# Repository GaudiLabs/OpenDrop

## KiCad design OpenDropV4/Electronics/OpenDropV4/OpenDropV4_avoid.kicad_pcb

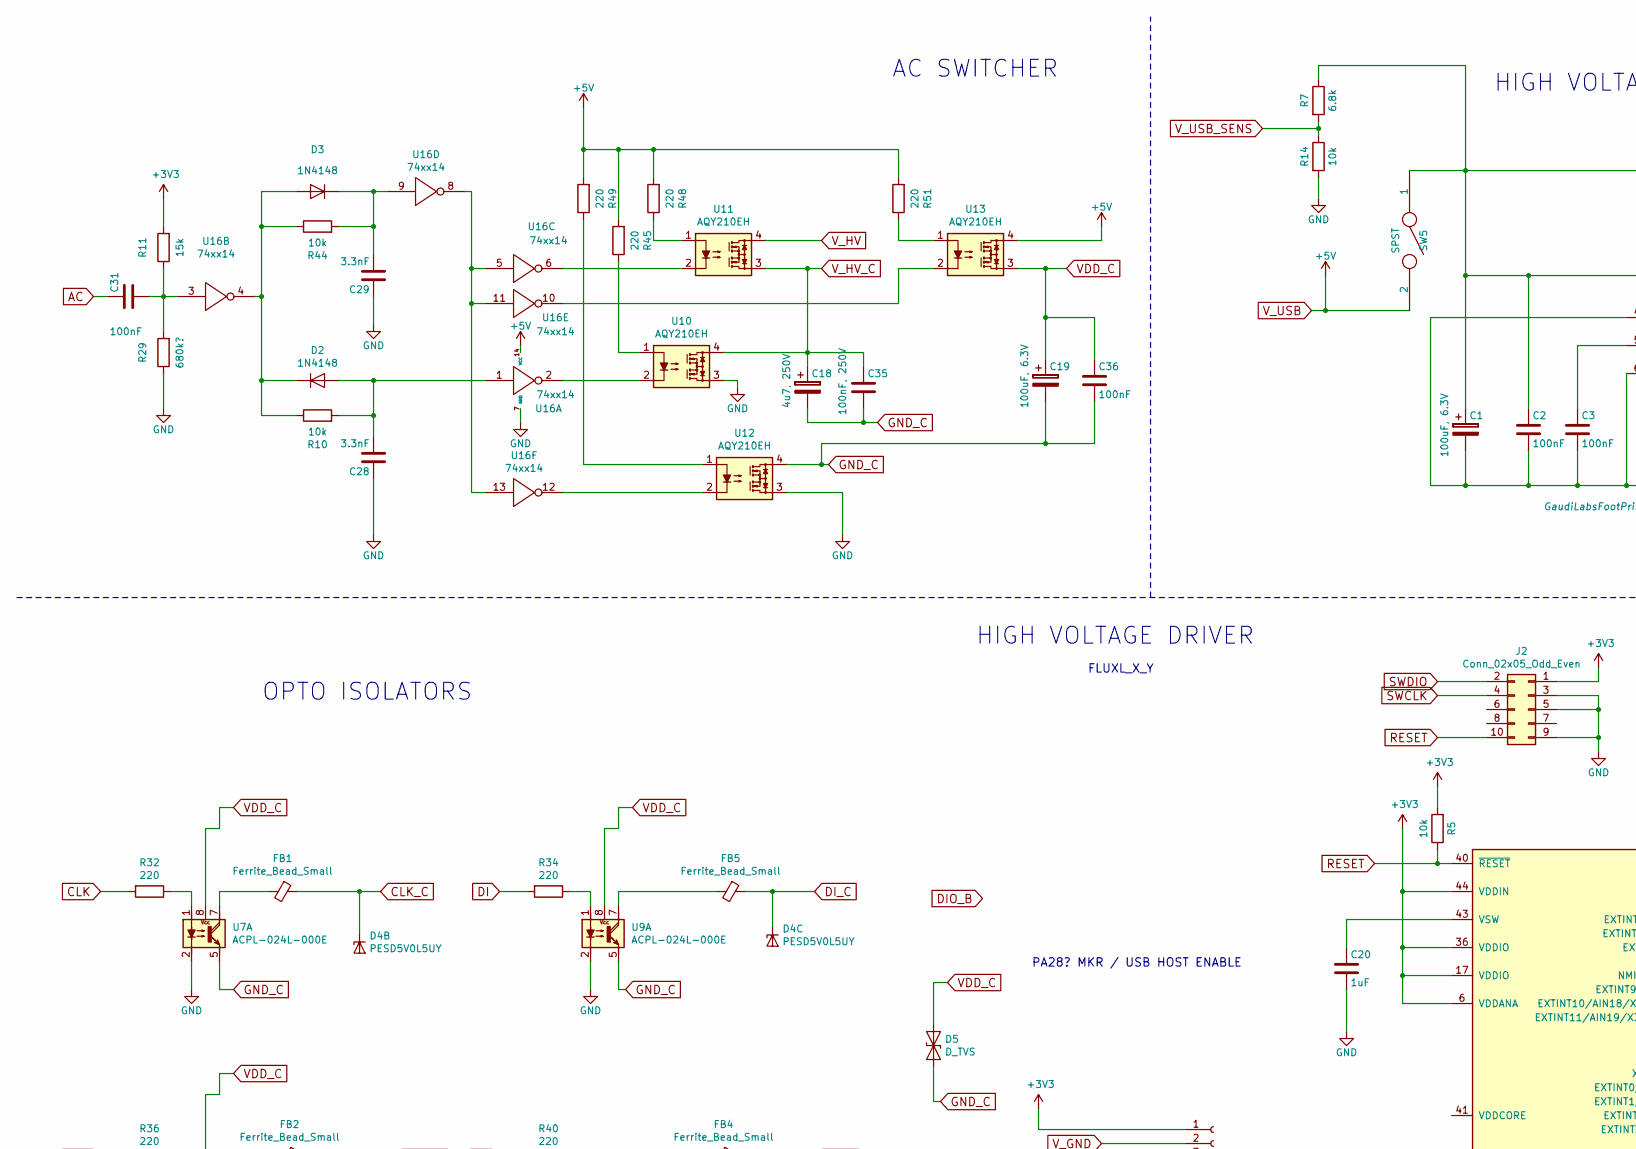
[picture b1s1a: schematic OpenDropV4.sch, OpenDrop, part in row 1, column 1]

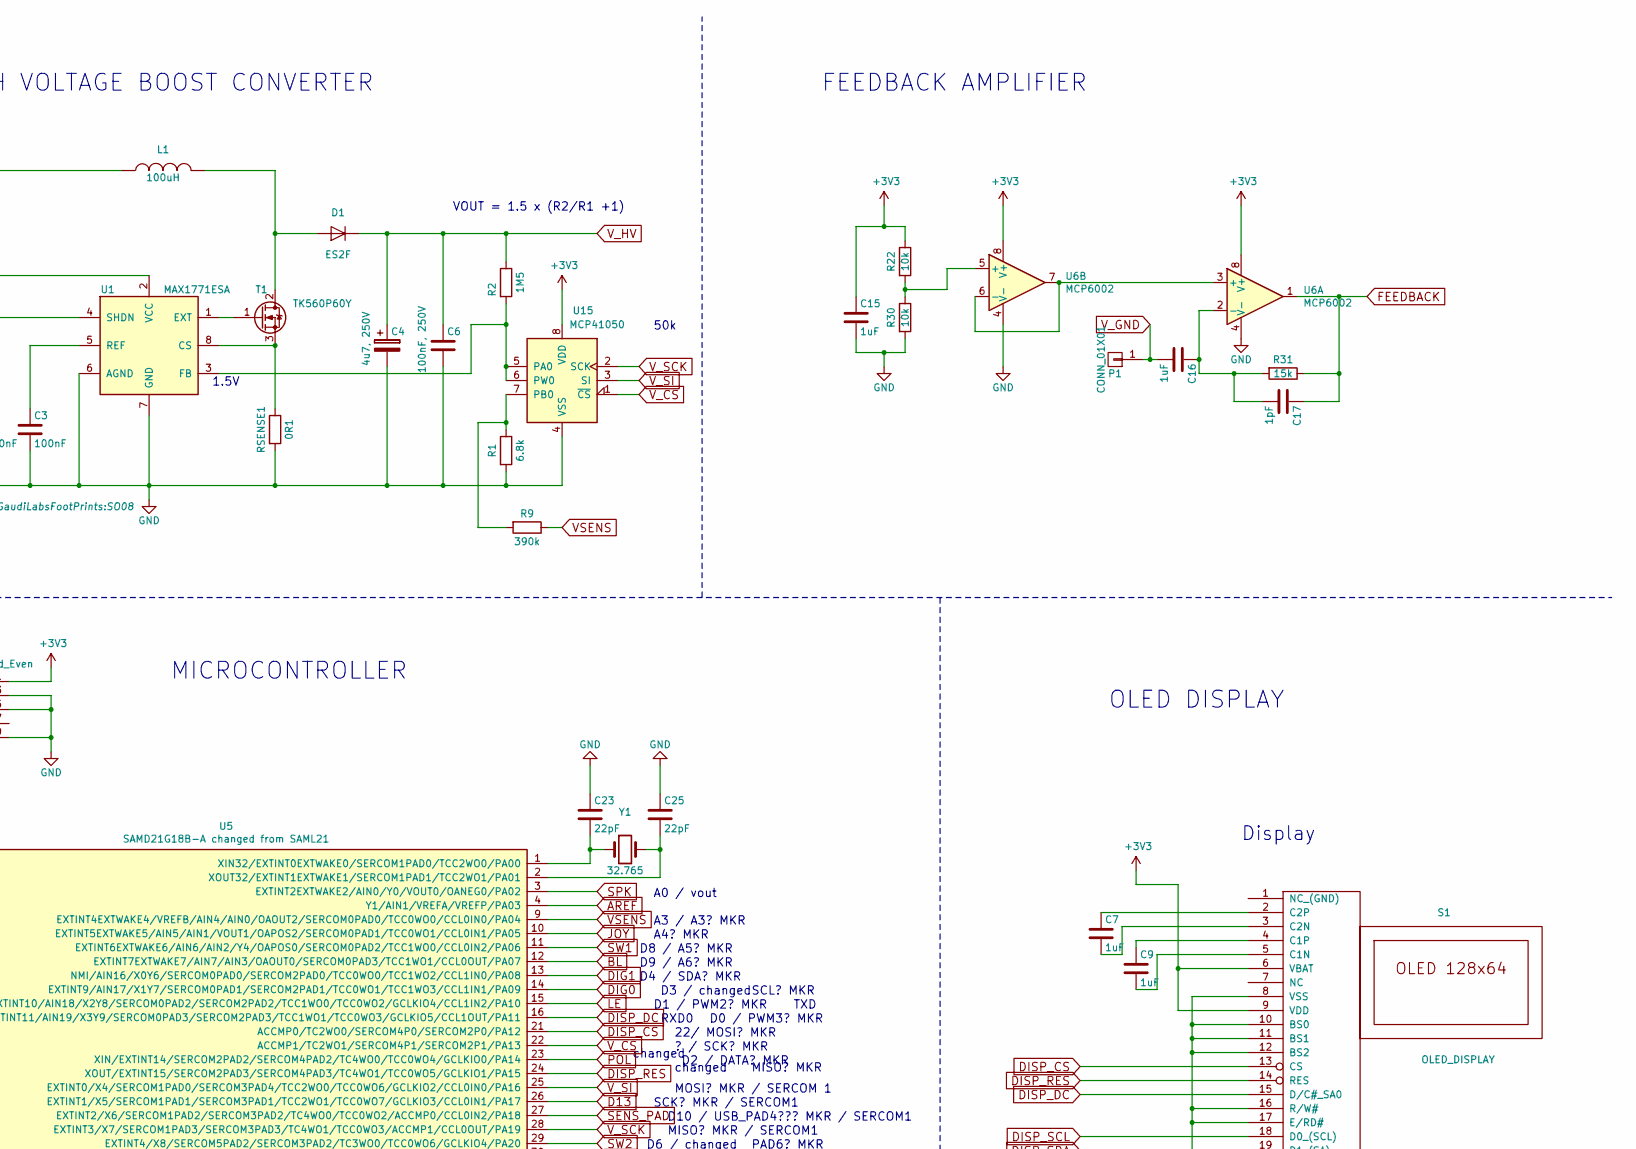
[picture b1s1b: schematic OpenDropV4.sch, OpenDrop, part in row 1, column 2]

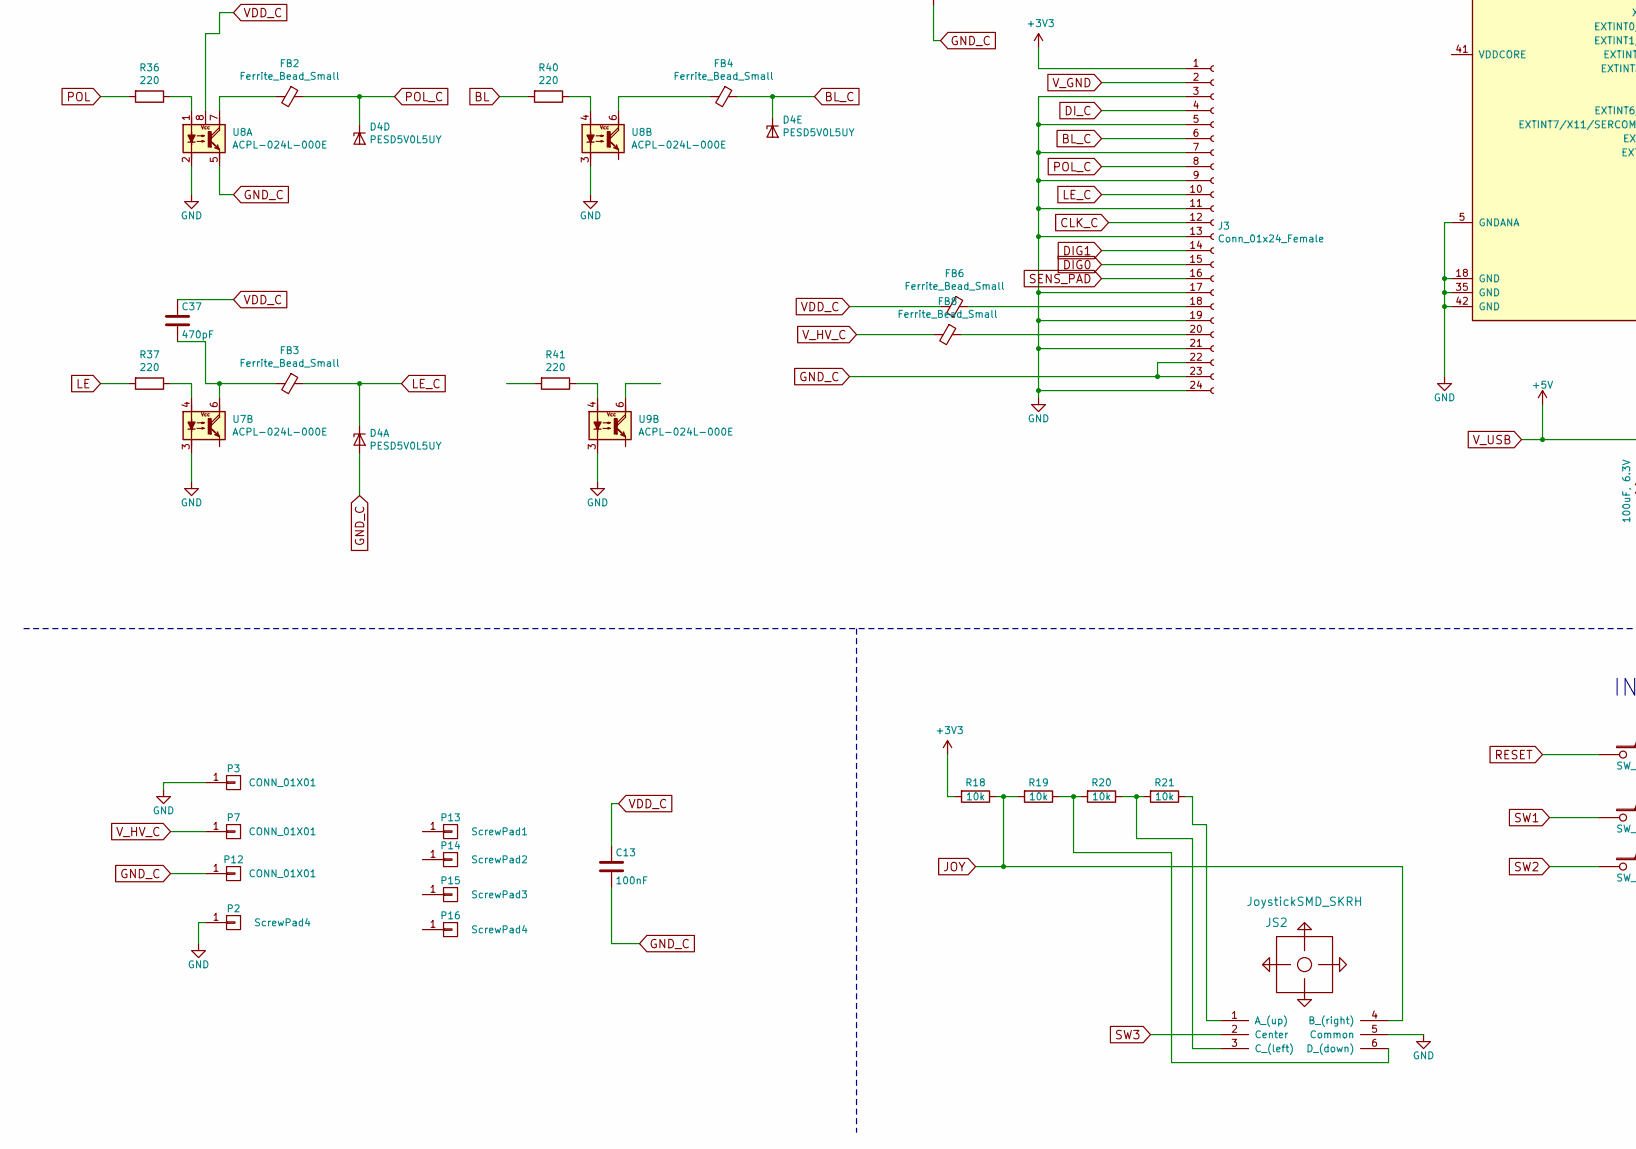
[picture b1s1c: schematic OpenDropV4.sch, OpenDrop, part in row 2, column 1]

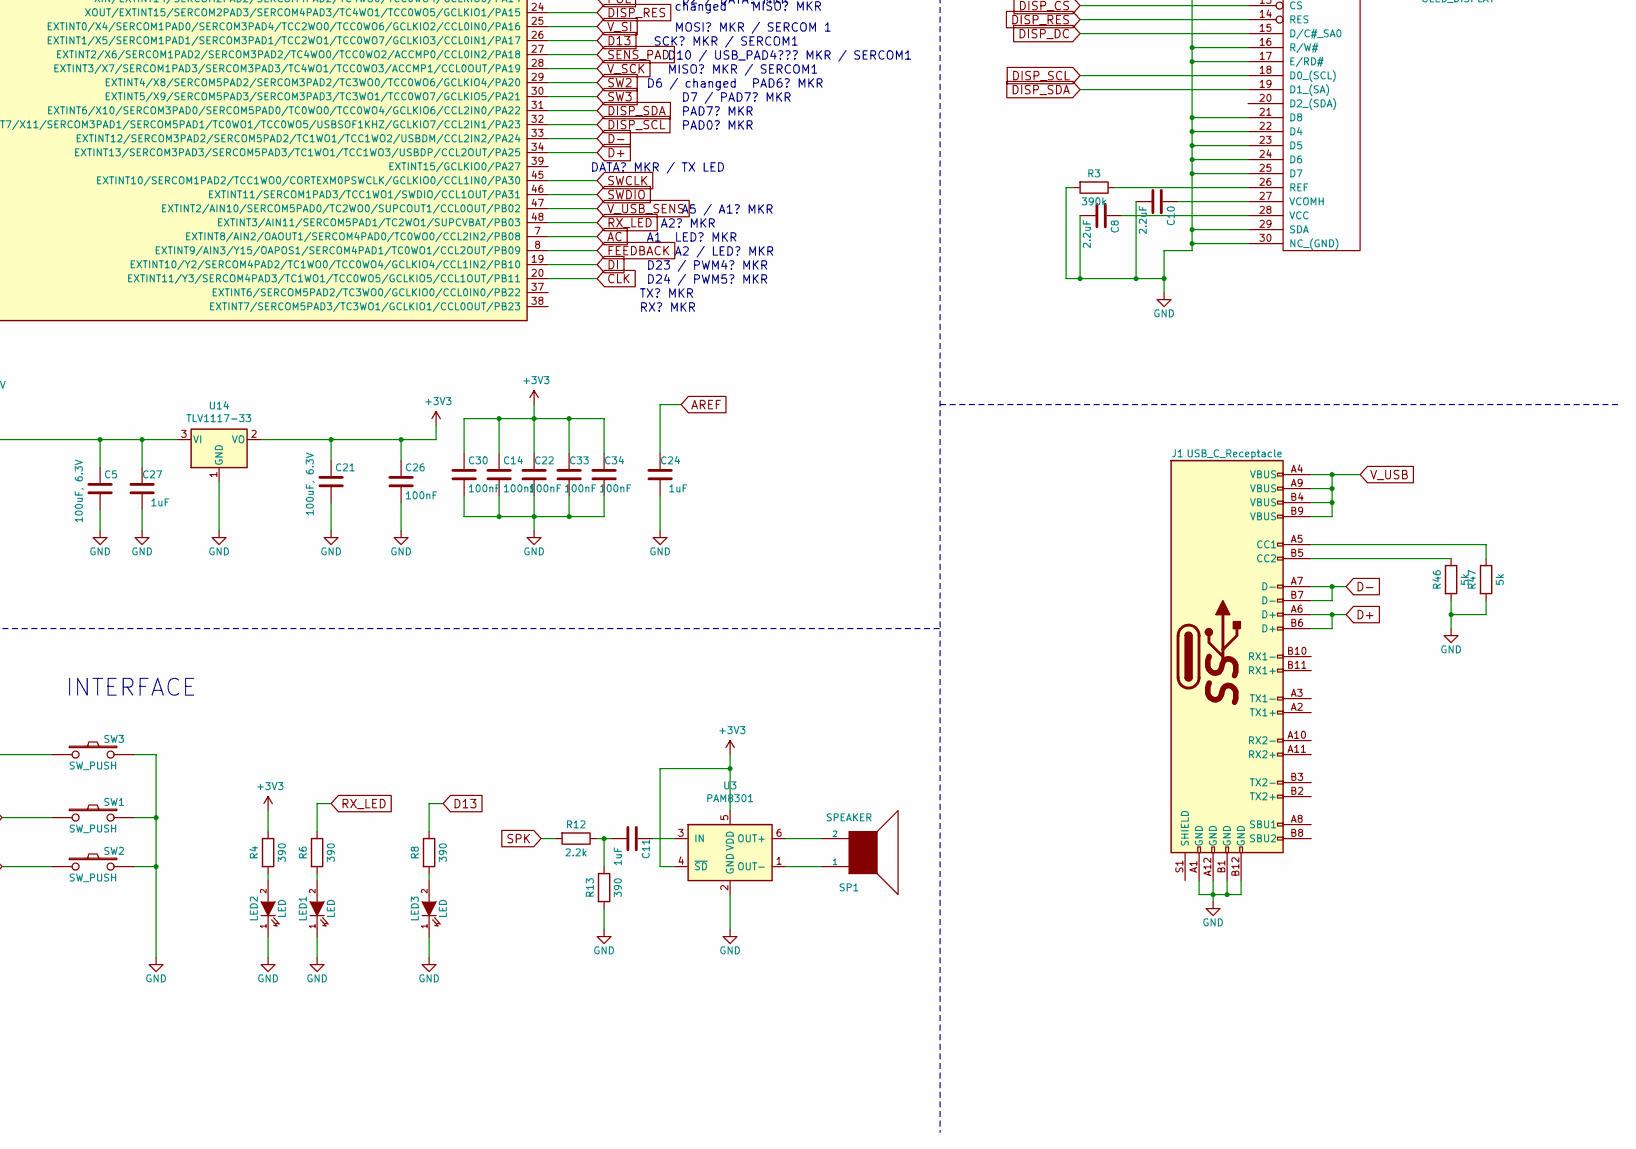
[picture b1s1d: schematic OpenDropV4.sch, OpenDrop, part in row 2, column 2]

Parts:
C1, C19: 100uF, 6.3V; C_1206_3216Metric
C2, C3, C13, C14, C22, C26, C30, C31, C33, C34, C36: 100nF; C_0805
C4, C18: 4u7, 250V; C_Elec_8x10.2
C5, C21: 100uF, 6.3V; C_1206
C6, C35: 100nF, 250V; C_1812_4532Metric_Pad1.30x3.40mm_HandSolder
C7, C9, C11, C15, C16, C20, C24, C27: 1uF; C_0805
C8, C10: 2.2uF; C_0805
C17: 1pF; C_0805
C23, C25: 22pF; C_0805
C28, C29: 3.3nF; C_0805
C37: 470pF; C_0805
D1: ES2F; DO-214AA
D2, D3: 1N4148; D_SOD-323
D4: PESD5V0L5UY; SOT-363_SC-70-6
D5: D_TVS; DO-214AA
FB1, FB2, FB3, FB4, FB5, FB6, FB8: Ferrite_Bead_Small; L_0603_1608Metric
J1: USB_C_Receptacle; USB_C_Receptacle_Amphenol_12401610E4-2A
J2: Conn_02x05_Odd_Even; Pin_Header_Straight_2x05_Pitch1.27mm_SMD
J3: Conn_01x24_Female; FFC_MOLEX_EASYON_05mm_24
JS2: JoystickSMD_SKRH; SKRHABE010
L1: 100uH; SRN1060
LED1, LED2, LED3: LED; LED_0603_1608Metric
P1, P3, P7, P12: CONN_01X01; Measurement_Point_Square-SMD-Pad_Small
P2: ScrewPad4; Measurement_Point_Croki
P13: ScrewPad1; MountingHoleM3
P14: ScrewPad2; MountingHoleM3
P15: ScrewPad3; MountingHoleM3
P16: ScrewPad4; MountingHoleM3
R1: 6.8k; R_0805
R2: 1M5; R_2512
R3, R9: 390k; R_0805
R4, R6, R8, R13: 390; R_0805
R5, R10, R18, R19, R20, R21, R22, R30, R44: 10k; R_0805
R7: 6.8k; R_0805_2012Metric
R11, R31: 15k; R_0805
R12: 2.2k; R_0805
R14: 10k; R_0805_2012Metric
R29: 680k?; R_0805
R32, R34, R36, R37, R40, R41, R45, R48, R49, R51: 220; R_0805
R46, R47: 5k; R_0805
RSENSE1: 0R1; R_2010
S1: OLED_DISPLAY; OLED_096_1_Flip
SP1: SPEAKER; Speaker16mm
SW1, SW2: SW_PUSH; PUSH_BUTTON_SMD
SW3: SW_PUSH; SW_SPST_KMS221GLFS
SW5: SPST; Switch_On-On
T1: TK560P60Y; D-Pak_TO252AA
U1: MAX1771ESA; SO08
U3: PAM8301; SOT-23-6
U5: SAMD21G18B-A changed from SAML21; TQFP-48_7x7mm_Pitch0.5mm
U6: MCP6002; SO08
U7, U8, U9: ACPL-024L-000E; HCPL_Optocoupler_SMD
U10, U11, U12, U13: AQY210EH; SMD_DIP4
U14: TLV1117-33; SOT-223
U15: MCP41050; SO08
U16: 74xx14; SOIC-14_N
Y1: 32.765; Crystal_SMD_3215-2pin_3.2x1.5mm

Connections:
+3V3: C14.1, C15.1, C21.1, C22.2, C26.1, C30.1, C33.2, C34.2, J2.1, J3.1, R4.1, R5.2, R11.2, R18.2, R22.1, S1.6 (VBAT), S1.9 (VDD), U3.4 (~SD), U3.5 (VDD), U5.6 (VDDANA), U5.17 (VDDIO), U5.36 (VDDIO), U5.44 (VDDIN), U6.8 (V+), U14.2 (VO), U15.8 (VDD)
AC: C31.1, U5.7 (EXTINT8/AIN2/OAOUT1/SERCOM4PAD0/TC0WO0/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)
AREF: C24.2, U5.4 (Y1/AIN1/VREFA/VREFP/PA03)
BL: R40.2, U5.12 (EXTINT7EXTWAKE7/AIN7/AIN3/OAOUT0/SERCOM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)
BL_C: D4.6 (K5), FB4.1, FB4.2, J3.6, U8.6 (COLLECTOR)
CLK: R32.2, U5.20 (EXTINT11/Y3/SERCOM4PAD3/TC1WO1/TCC0WO5/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)
CLK_C: D4.3 (K2), FB1.1, FB1.2, J3.12, U7.7 (COLLECTOR)
D13: R8.1, U5.26 (EXTINT1/X5/SERCOM1PAD1/SERCOM3PAD1/TCC2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)
D+: J1.A6 (D+), J1.B6 (D+), U5.34 (EXTINT13/SERCOM3PAD3/SERCOM5PAD3/TC1WO1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)
D-: J1.A7 (D-), J1.B7 (D-), U5.33 (EXTINT12/SERCOM3PAD2/SERCOM5PAD2/TC1WO1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)
DI: R34.2, U5.19 (EXTINT10/Y2/SERCOM4PAD2/TC1WO0/TCC0WO4/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)
DIG0: J3.15, U5.14 (EXTINT9/AIN17/X1Y7/SERCOM0PAD1/SERCOM2P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)
DISP_CS: S1.13 (CS), U5.21 (ACCMP0/TC2WO0/SERCOM4P0/SERCOM2P0/PA12)
DISP_DC: S1.15 (D/C#_SA0), U5.16 (EXTINT11/AIN19/X3Y9/SERCOM0PAD3/SERCOM2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)
DISP_RES: S1.14 (RES), U5.24 (XOUT/EXTINT15/SERCOM2PAD3/SERCOM4PAD3/T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)
DISP_SCL: S1.18 (D0_(SCL)), U5.32 (EXTINT7/X11/SERCOM3PAD1/SERCOM5PAD1/TC0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)
DISP_SDA: S1.19 (D1_(SA)), U5.31 (EXTINT6/X10/SERCOM3PAD0/SERCOM5PAD0/TC0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)
DI_C: D4.4 (K3), FB5.1, FB5.2, J3.4, U9.7 (COLLECTOR)
FEEDBACK: C17.1, R31.1, U5.8 (EXTINT9/AIN3/Y15/OAPOS1/SERCOM4PAD1/TC0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), U6.1
GND: C1.2, C2.2, C3.2, C4.2, C5.2, C6.2, C8.2, C10.2, C14.2, C15.2, C20.2, C21.2, C22.1, C23.1, C24.1, C25.1, C26.2, C27.1, C28.1, C29.1, C30.2, C33.1, C34.1, J1.A1 (GND), J1.A12 (GND), J1.B1 (GND), J1.B12 (GND), J2.3, J2.5, J2.9, J3.3, J3.5, J3.7, J3.9, J3.11, J3.13, J3.17, J3.19, J3.21, J3.24, JS2.5 (Common), LED1.1 (K), LED2.1 (K), LED3.1 (K), P2.1, P3.1, R1.2, R3.2, R13.2, R14.2, R29.1, R30.2, R46.2, R47.2, RSENSE1.2, S1.8 (VSS), S1.10 (BS0), S1.11 (BS1), S1.12 (BS2), S1.16 (R/W#), S1.17 (E/RD#), S1.21 (D8), S1.22 (D4), S1.23 (D5), S1.24 (D6), S1.25 (D7), S1.29 (SDA), S1.30 (NC_(GND)), SW1.2, SW2.2, SW3.2, U1.4 (SHDN), U1.6 (AGND), U1.7 (GND), U3.2 (GND), U5.5 (GNDANA), U5.18 (GND), U5.35 (GND), U5.42 (GND), U6.4 (V-), U7.2 (CATHODE), U7.3 (CATHODE), U8.2 (CATHODE), U8.3 (CATHODE), U9.2 (CATHODE), U9.3 (CATHODE), U10.3, U12.3, U14.1 (GND), U15.4 (VSS), U16.7 (GND)
GND_C: C13.2, C18.2, C19.2, C35.2, C36.2, D4.2 (A), D5.2 (A2), J3.22, J3.23, P12.1, U7.5, U8.5, U9.5, U12.4
JOY: JS2.4 (B_(right)), R18.1, R19.2, U5.10 (EXTINT5EXTWAKE5/AIN5/AIN1/VOUT1/OAPOS2/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)
unnamed: C1.1, C2.1, L1.1, R7.1, SW5.1, U1.2 (VCC)
unnamed: C3.1, U1.5 (REF)
unnamed: C7.1, S1.2 (C2P)
unnamed: C7.2, S1.3 (C2N)
unnamed: C8.1, S1.28 (VCC)
unnamed: C9.1, S1.4 (C1P)
unnamed: C9.2, S1.5 (C1N)
unnamed: C10.1, S1.27 (VCOMH)
unnamed: C11.1, R12.1, R13.1
unnamed: C11.2, U3.3 (IN)
unnamed: C16.1, C17.2, R31.2, U6.2 (-)
unnamed: C20.1, U5.43 (VSW)
unnamed: C23.2, U5.1 (XIN32/EXTINT0EXTWAKE0/SERCOM1PAD0/TCC2W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), Y1.1
unnamed: C25.2, U5.2 (XOUT32/EXTINT1EXTWAKE1/SERCOM1PAD1/TCC2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), Y1.2
unnamed: C28.2, D2.2 (A), R10.2, U16.1
unnamed: C29.2, D3.1 (K), R44.2, U16.9
unnamed: C31.2, R11.1, R29.2, U16.3
unnamed: D1.2 (A), L1.2, T1.2 (D)
unnamed: D2.1 (K), D3.2 (A), R10.1, R44.1, U16.4
unnamed: J1.A5 (CC1), R47.1
unnamed: J1.B5 (CC2), R46.1
unnamed: JS2.1 (A_(up)), R21.1
unnamed: JS2.3 (C_(left)), R20.1, R21.2
unnamed: JS2.6 (D_(down)), R19.1, R20.2
unnamed: LED1.2 (A), R6.2
unnamed: LED2.2 (A), R4.2
unnamed: LED3.2 (A), R8.2
unnamed: R1.1, R9.2, U15.7 (PB0)
unnamed: R2.2, U1.3 (FB), U15.5 (PA0), U15.6 (PW0)
unnamed: R3.1, S1.26 (REF)
unnamed: R7.2, R14.1, U5.47 (EXTINT2/AIN10/SERCOM5PAD0/TC2WO0/SUPCOU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)
unnamed: R22.2, R30.1, U6.5 (+)
unnamed: R32.1, U7.1 (ANODE)
unnamed: R34.1, U9.1 (ANODE)
unnamed: R36.1, U8.1 (ANODE)
unnamed: R37.1, U7.4 (ANODE)
unnamed: R40.1, U8.4 (ANODE)
unnamed: R41.1, U9.4 (ANODE)
unnamed: R45.1, U10.1
unnamed: R48.1, U11.1
unnamed: R49.1, U12.1
unnamed: R51.1, U13.1
unnamed: RSENSE1.1, T1.3 (S), U1.8 (CS)
unnamed: SP1.1, U3.1 (OUT-)
unnamed: SP1.2, U3.6 (OUT+)
unnamed: T1.1 (G), U1.1 (EXT)
unnamed: U6.3 (+), U6.6 (-), U6.7
unnamed: U10.2, U16.2
unnamed: U11.2, U16.6
unnamed: U12.2, U16.12
unnamed: U13.2, U16.10
unnamed: U16.5, U16.8, U16.11, U16.13
POL: R36.2, U5.23 (XIN/EXTINT14/SERCOM2PAD2/SERCOM4PAD2/TC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)
POL_C: D4.5 (K4), FB2.1, FB2.2, J3.8, U8.7 (COLLECTOR)
RESET: J2.10, R5.1, SW3.1, U5.40 (~RESET~)
RX_LED: R6.1, U5.48 (EXTINT3/AIN11/SERCOM5PAD1/TC2WO1/SUPCVB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)
SENS_PAD: J3.16, U5.27 (EXTINT2/X6/SERCOM1PAD2/SERCOM3PAD2/TC4W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)
SPK: R12.2, U5.3 (EXTINT2EXTWAKE2/AIN0/Y0/VOUT0/OANEG0/PA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)
SW1: SW1.1, U5.11 (EXTINT6EXTWAKE6/AIN6/AIN2/Y4/OAPOS0/SER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)
SW2: SW2.1, U5.29 (EXTINT4/X8/SERCOM5PAD2/SERCOM3PAD2/TC3W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)
SW3: JS2.2 (Center), U5.30 (EXTINT5/X9/SERCOM5PAD3/SERCOM3PAD3/TC3W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)
SWCLK: J2.4, U5.45 (EXTINT10/SERCOM1PAD2/TCC1WO0/CORTEXM0PS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)
SWDIO: J2.2, U5.46 (EXTINT11/SERCOM1PAD3/TCC1WO1/SWDIO/CCL1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)
VDD_C: C13.1, C19.1, C36.1, C37.1, D5.1 (A1), FB6.1, FB6.2, J3.18, U7.8 (VCC), U8.8 (VCC), U9.8 (VCC), U13.3
VSENS: R9.1, U5.9 (EXTINT4EXTWAKE4/VREFB/AIN4/AIN0/OAOUT2/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)
V_CS: U5.22 (ACCMP1/TC2WO1/SERCOM4P1/SERCOM2P1/PA13), U15.1 (~CS)
V_GND: C16.2, J3.2, P1.1
V_HV: C4.1, C6.1, D1.1 (K), R2.1, U11.4
V_HV_C: C18.1, C35.1, FB8.1, FB8.2, J3.20, P7.1, U10.4, U11.3
V_SCK: U5.28 (EXTINT3/X7/SERCOM1PAD3/SERCOM3PAD3/TC4W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), U15.2 (SCK)
V_SI: U5.25 (EXTINT0/X4/SERCOM1PAD0/SERCOM3PAD4/TCC2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), U15.3 (SI)
V_USB: C5.1, C27.2, J1.A4 (VBUS), J1.A9 (VBUS), J1.B4 (VBUS), J1.B9 (VBUS), R45.2, R48.2, R49.2, R51.2, SW5.2, U13.4, U14.3 (VI), U16.14 (VCC)

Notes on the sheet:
VOUT = 1.5 x (R2/R1 +1)
Display
AC SWITCHER
HIGH VOLTAGE BOOST CONVERTER
FEEDBACK AMPLIFIER
INTERFACE
HIGH VOLTAGE DRIVER
OPTO ISOLATORS
MICROCONTROLLER
OLED DISPLAY
D6 / changed
A0 / vout
changed
50k
D3 / changed
LED? MKR
A3 / A3? MKR
A4? MKR
D8 / A5? MKR
D9 / A6? MKR
D4 / SDA? MKR
SCL? MKR
D1 / PWM2? MKR
D0 / PWM3? MKR
D23 / PWM4? MKR
D24 / PWM5? MKR
22/ MOSI? MKR
? / SCK? MKR
D2 / DATA? MKR
MISO? MKR
MOSI? MKR / SERCOM 1
SCK? MKR / SERCOM1
D10 / USB_PAD4??? MKR / SERCOM1
MISO? MKR / SERCOM1
PAD6? MKR
D7 / PAD7? MKR
PAD7? MKR
PAD0? MKR
TX? MKR
RX? MKR

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
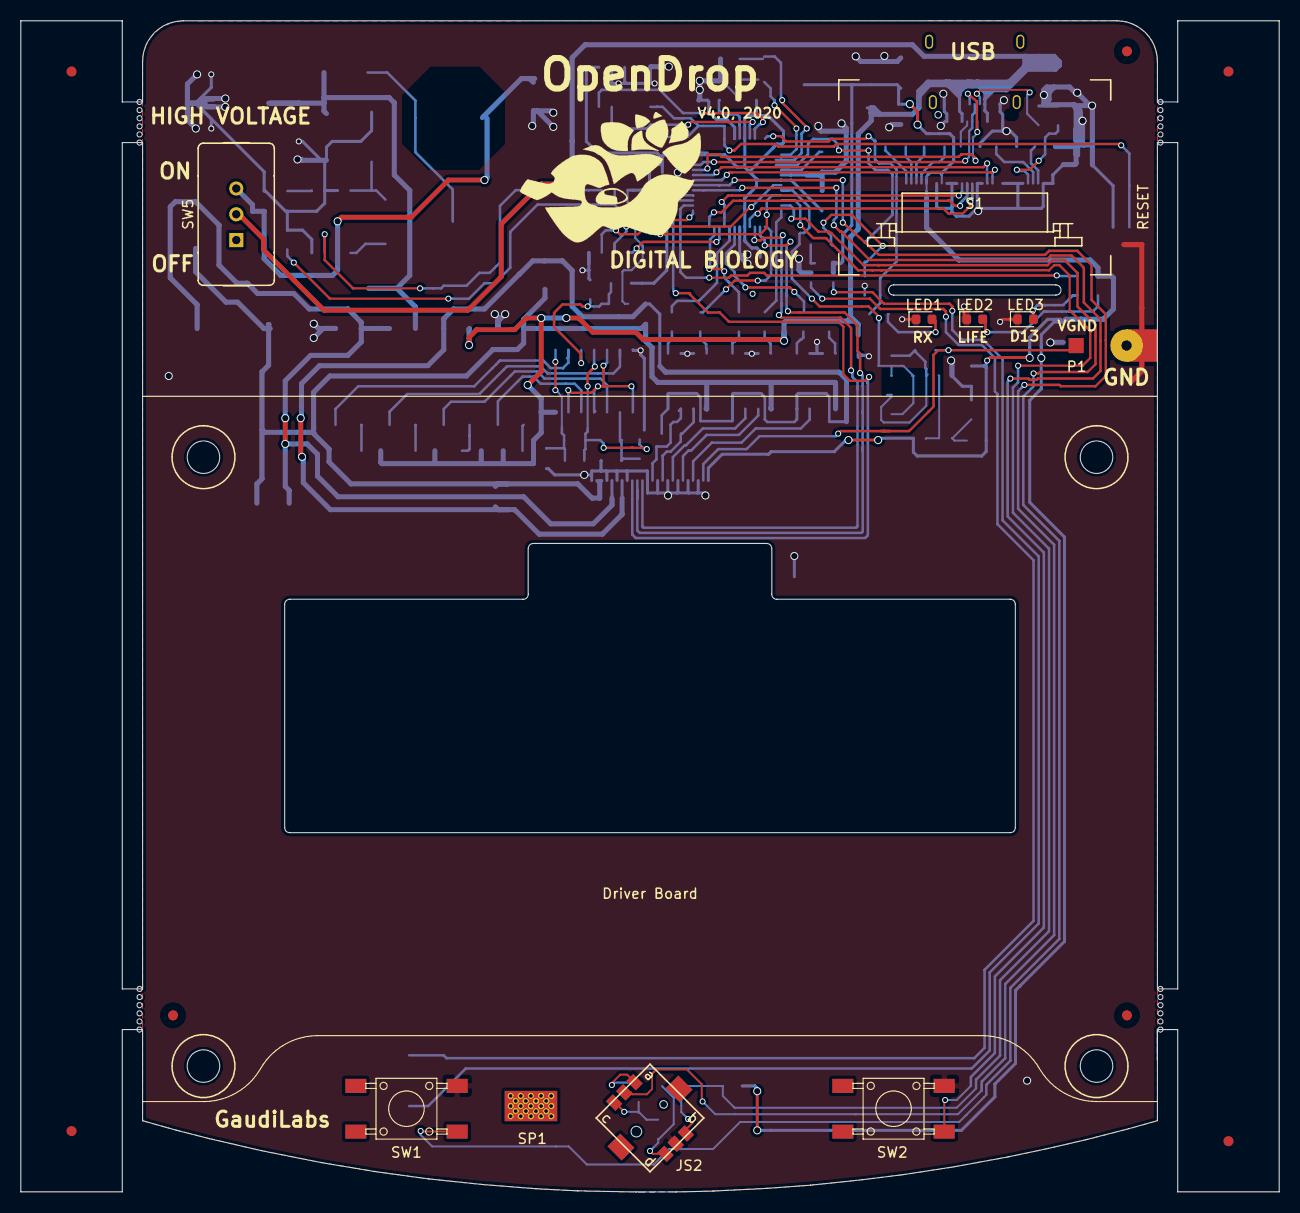
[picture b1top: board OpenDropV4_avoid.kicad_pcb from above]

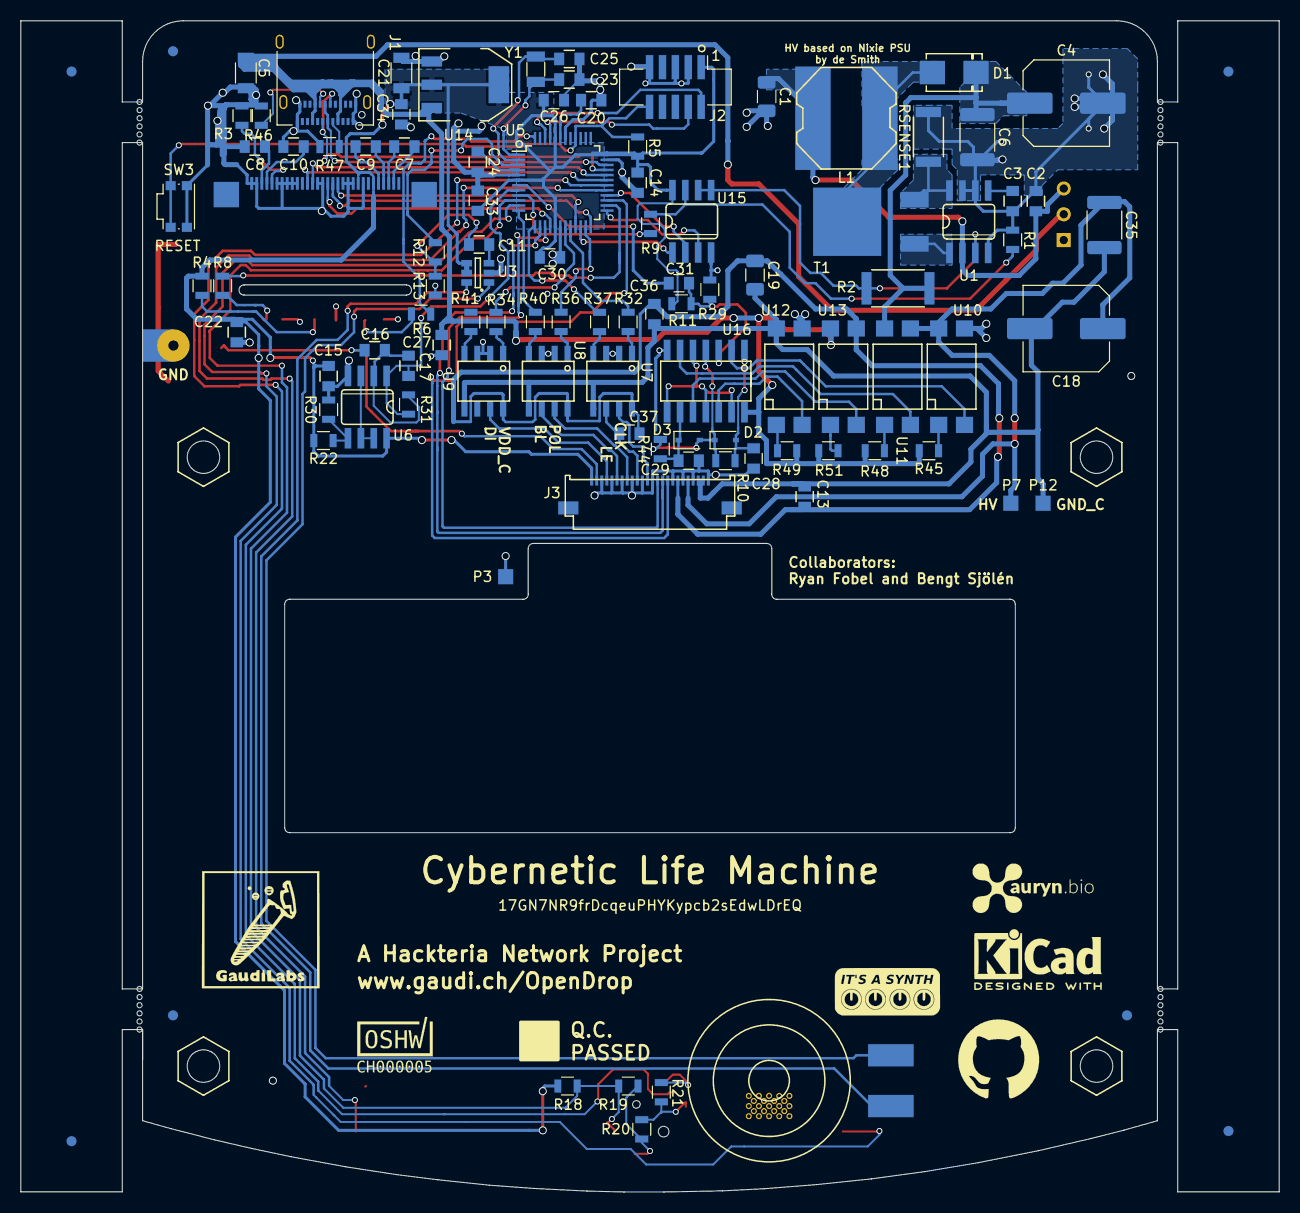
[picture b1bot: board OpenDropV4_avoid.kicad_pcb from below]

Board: 2 copper layers, 124.0 x 115.4 mm, 111 parts (96 on the bottom side), 96 nets.

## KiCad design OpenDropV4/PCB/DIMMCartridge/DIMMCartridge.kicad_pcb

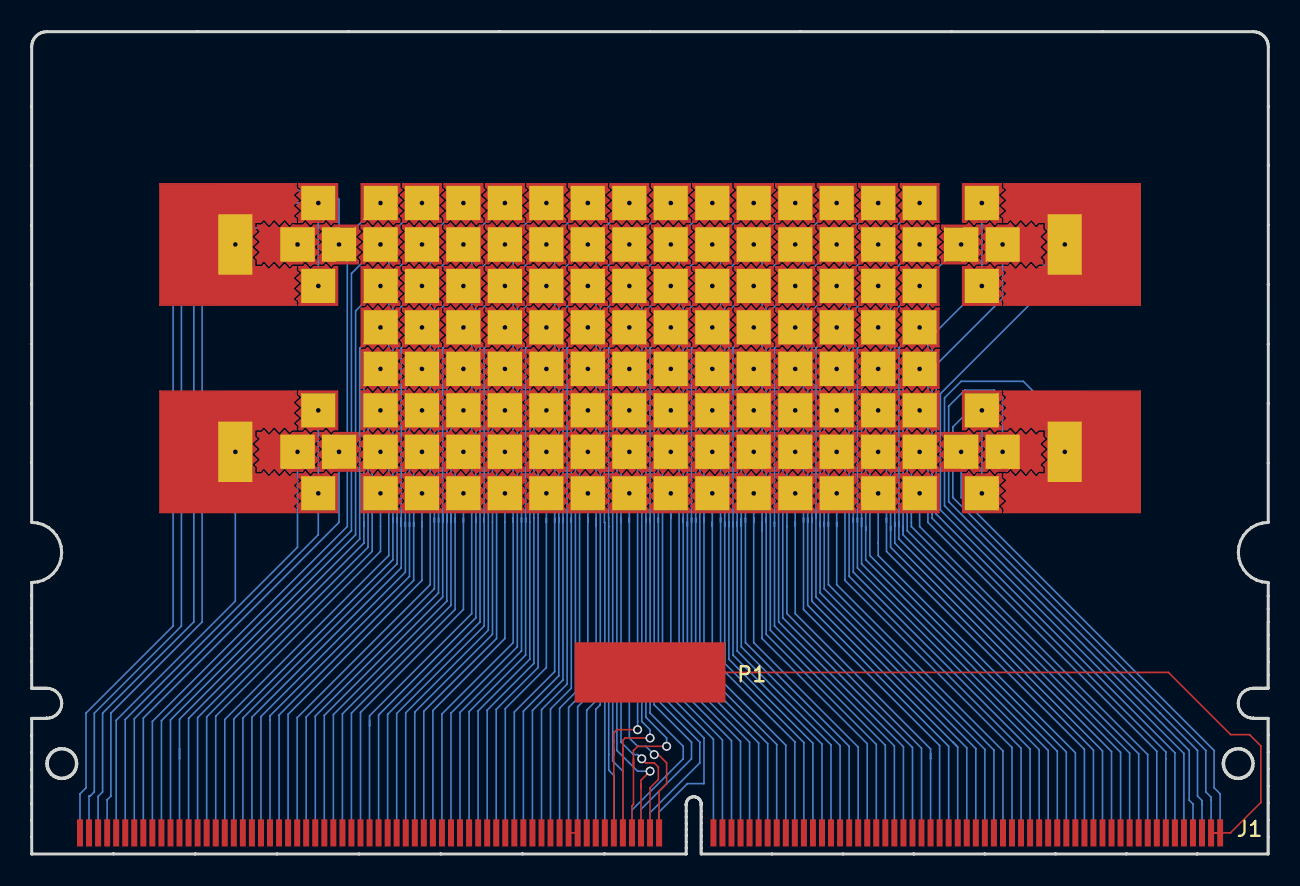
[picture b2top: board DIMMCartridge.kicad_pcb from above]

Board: 2 copper layers, 82.0 x 54.5 mm, 134 parts (0 on the bottom side), 130 nets.

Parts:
FLUXL_1_1, FLUXL_1_8, FLUXL_16_1, FLUXL_16_8: FX; FLUXPAD_2_75_4MIL_4_5_res1
FLUXL_1_2, FLUXL_1_7, FLUXL_16_2, FLUXL_16_7: FX; FLUXPAD_2_75_4MIL_4_5_res4
FLUXL_1_2b1, FLUXL_1_7b1, FLUXL_16_2b1, FLUXL_16_7b1: FX; FLUXPAD_2_75_4MIL_4_5_res5
FLUXL_1_3, FLUXL_1_6, FLUXL_16_3, FLUXL_16_6: FX; FLUXPAD_2_75_4MIL_4_5_res2
FLUXL_1_4, FLUXL_1_5, FLUXL_16_4, FLUXL_16_5: FX; FLUXPAD_2_75_4MIL_4_5_res3
FLUXL_2_1, FLUXL_15_8: FX; FLUXPAD_2_75_4MIL_4_5_topleft
FLUXL_2_2, FLUXL_2_7, FLUXL_3_2, FLUXL_3_3, FLUXL_3_4, FLUXL_3_5, FLUXL_3_6, FLUXL_3_7, FLUXL_4_2, FLUXL_4_3, FLUXL_4_4, FLUXL_4_5, FLUXL_4_6, FLUXL_4_7, FLUXL_5_2, FLUXL_5_3, FLUXL_5_4, FLUXL_5_5, FLUXL_5_6, FLUXL_5_7, FLUXL_6_2, FLUXL_6_3, FLUXL_6_4, FLUXL_6_5, FLUXL_6_6, FLUXL_6_7, FLUXL_7_2, FLUXL_7_3, FLUXL_7_4, FLUXL_7_5, FLUXL_7_6, FLUXL_7_7, FLUXL_8_2, FLUXL_8_3, FLUXL_8_4, FLUXL_8_5, FLUXL_8_6, FLUXL_8_7, FLUXL_9_2, FLUXL_9_3, FLUXL_9_4, FLUXL_9_5, FLUXL_9_6, FLUXL_9_7, FLUXL_10_2, FLUXL_10_3, FLUXL_10_4, FLUXL_10_5, FLUXL_10_6, FLUXL_10_7, FLUXL_11_2, FLUXL_11_3, FLUXL_11_4, FLUXL_11_5, FLUXL_11_6, FLUXL_11_7, FLUXL_12_2, FLUXL_12_3, FLUXL_12_4, FLUXL_12_5, FLUXL_12_6, FLUXL_12_7, FLUXL_13_2, FLUXL_13_3, FLUXL_13_4, FLUXL_13_5, FLUXL_13_6, FLUXL_13_7, FLUXL_14_2, FLUXL_14_3, FLUXL_14_4, FLUXL_14_5, FLUXL_14_6, FLUXL_14_7, FLUXL_15_2, FLUXL_15_7: FX; FLUXPAD_2_75_4MIL_4_5
FLUXL_2_3, FLUXL_2_4, FLUXL_2_5, FLUXL_2_6, FLUXL_15_3, FLUXL_15_4, FLUXL_15_5, FLUXL_15_6: FX; FLUXPAD_2_75_4MIL_4_5_side
FLUXL_2_8, FLUXL_15_1: FX; FLUXPAD_2_75_4MIL_4_5_topright
FLUXL_3_1, FLUXL_3_8, FLUXL_4_1, FLUXL_4_8, FLUXL_5_1, FLUXL_5_8, FLUXL_6_1, FLUXL_6_8, FLUXL_7_1, FLUXL_7_8, FLUXL_8_1, FLUXL_8_8, FLUXL_9_1, FLUXL_9_8, FLUXL_10_1, FLUXL_10_8, FLUXL_11_1, FLUXL_11_8, FLUXL_12_1, FLUXL_12_8, FLUXL_13_1, FLUXL_13_8, FLUXL_14_1, FLUXL_14_8: FX; FLUXPAD_2_75_4MIL_4_5_top
J1: Mini_Dimm_244; Mini_Dimm_Cartridge_06_244
P1: V_GND; Pad_4mm_10mm

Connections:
unnamed: FLUXL_1_1.1, J1.244
unnamed: FLUXL_1_2.1, FLUXL_1_2b1.1, J1.243
unnamed: FLUXL_1_3.1, J1.242
unnamed: FLUXL_1_4.1, J1.241
unnamed: FLUXL_1_5.1, J1.240
unnamed: FLUXL_1_6.1, J1.239
unnamed: FLUXL_1_7.1, FLUXL_1_7b1.1, J1.238
unnamed: FLUXL_1_8.1, J1.237
unnamed: FLUXL_2_1.1, J1.236
unnamed: FLUXL_2_2.1, J1.235
unnamed: FLUXL_2_3.1, J1.234
unnamed: FLUXL_2_4.1, J1.233
unnamed: FLUXL_2_5.1, J1.232
unnamed: FLUXL_2_6.1, J1.231
unnamed: FLUXL_2_7.1, J1.230
unnamed: FLUXL_2_8.1, J1.229
unnamed: FLUXL_3_1.1, J1.228
unnamed: FLUXL_3_2.1, J1.227
unnamed: FLUXL_3_3.1, J1.226
unnamed: FLUXL_3_4.1, J1.225
unnamed: FLUXL_3_5.1, J1.224
unnamed: FLUXL_3_6.1, J1.223
unnamed: FLUXL_3_7.1, J1.222
unnamed: FLUXL_3_8.1, J1.221
unnamed: FLUXL_4_1.1, J1.220
unnamed: FLUXL_4_2.1, J1.219
unnamed: FLUXL_4_3.1, J1.218
unnamed: FLUXL_4_4.1, J1.217
unnamed: FLUXL_4_5.1, J1.216
unnamed: FLUXL_4_6.1, J1.215
unnamed: FLUXL_4_7.1, J1.214
unnamed: FLUXL_4_8.1, J1.213
unnamed: FLUXL_5_1.1, J1.212
unnamed: FLUXL_5_2.1, J1.211
unnamed: FLUXL_5_3.1, J1.210
unnamed: FLUXL_5_4.1, J1.209
unnamed: FLUXL_5_5.1, J1.208
unnamed: FLUXL_5_6.1, J1.207
unnamed: FLUXL_5_7.1, J1.206
unnamed: FLUXL_5_8.1, J1.205
unnamed: FLUXL_6_1.1, J1.204
unnamed: FLUXL_6_2.1, J1.203
unnamed: FLUXL_6_3.1, J1.202
unnamed: FLUXL_6_4.1, J1.201
unnamed: FLUXL_6_5.1, J1.200
unnamed: FLUXL_6_6.1, J1.199
unnamed: FLUXL_6_7.1, J1.198
unnamed: FLUXL_6_8.1, J1.197
unnamed: FLUXL_7_1.1, J1.196
unnamed: FLUXL_7_2.1, J1.195
unnamed: FLUXL_7_3.1, J1.194
unnamed: FLUXL_7_4.1, J1.193
unnamed: FLUXL_7_5.1, J1.192
unnamed: FLUXL_7_6.1, J1.191
unnamed: FLUXL_7_7.1, J1.190
unnamed: FLUXL_7_8.1, J1.189
unnamed: FLUXL_8_1.1, J1.188
unnamed: FLUXL_8_2.1, J1.187
unnamed: FLUXL_8_3.1, J1.186
unnamed: FLUXL_8_4.1, J1.185
unnamed: FLUXL_8_5.1, J1.184
unnamed: FLUXL_8_6.1, J1.63
unnamed: FLUXL_8_7.1, J1.64
unnamed: FLUXL_8_8.1, J1.65
unnamed: FLUXL_9_1.1, J1.60
unnamed: FLUXL_9_2.1, J1.61
unnamed: FLUXL_9_3.1, J1.62
unnamed: FLUXL_9_4.1, J1.183
unnamed: FLUXL_9_5.1, J1.182
unnamed: FLUXL_9_6.1, J1.181
unnamed: FLUXL_9_7.1, J1.180
unnamed: FLUXL_9_8.1, J1.179
unnamed: FLUXL_10_1.1, J1.178
unnamed: FLUXL_10_2.1, J1.177
unnamed: FLUXL_10_3.1, J1.176
unnamed: FLUXL_10_4.1, J1.175
unnamed: FLUXL_10_5.1, J1.174
unnamed: FLUXL_10_6.1, J1.173
unnamed: FLUXL_10_7.1, J1.172
unnamed: FLUXL_10_8.1, J1.171
unnamed: FLUXL_11_1.1, J1.170
unnamed: FLUXL_11_2.1, J1.169
unnamed: FLUXL_11_3.1, J1.168
unnamed: FLUXL_11_4.1, J1.167
unnamed: FLUXL_11_5.1, J1.166
unnamed: FLUXL_11_6.1, J1.165
unnamed: FLUXL_11_7.1, J1.164
unnamed: FLUXL_11_8.1, J1.163
unnamed: FLUXL_12_1.1, J1.162
unnamed: FLUXL_12_2.1, J1.161
unnamed: FLUXL_12_3.1, J1.160
unnamed: FLUXL_12_4.1, J1.159
unnamed: FLUXL_12_5.1, J1.158
unnamed: FLUXL_12_6.1, J1.157
unnamed: FLUXL_12_7.1, J1.156
unnamed: FLUXL_12_8.1, J1.155
unnamed: FLUXL_13_1.1, J1.154
unnamed: FLUXL_13_2.1, J1.153
unnamed: FLUXL_13_3.1, J1.152
unnamed: FLUXL_13_4.1, J1.151
unnamed: FLUXL_13_5.1, J1.150
unnamed: FLUXL_13_6.1, J1.149
unnamed: FLUXL_13_7.1, J1.148
unnamed: FLUXL_13_8.1, J1.147
unnamed: FLUXL_14_1.1, J1.146
unnamed: FLUXL_14_2.1, J1.145
unnamed: FLUXL_14_3.1, J1.144
unnamed: FLUXL_14_4.1, J1.143
unnamed: FLUXL_14_5.1, J1.142
unnamed: FLUXL_14_6.1, J1.141
unnamed: FLUXL_14_7.1, J1.140
unnamed: FLUXL_14_8.1, J1.139
unnamed: FLUXL_15_1.1, J1.138
unnamed: FLUXL_15_2.1, J1.137
unnamed: FLUXL_15_3.1, J1.136
unnamed: FLUXL_15_4.1, J1.135
unnamed: FLUXL_15_5.1, J1.134
unnamed: FLUXL_15_6.1, J1.133
unnamed: FLUXL_15_7.1, J1.132
unnamed: FLUXL_15_8.1, J1.131
unnamed: FLUXL_16_1.1, J1.130
unnamed: FLUXL_16_2.1, FLUXL_16_2b1.1, J1.129
unnamed: FLUXL_16_3.1, J1.128
unnamed: FLUXL_16_4.1, J1.127
unnamed: FLUXL_16_5.1, J1.126
unnamed: FLUXL_16_6.1, J1.125
unnamed: FLUXL_16_7.1, FLUXL_16_7b1.1, J1.124
unnamed: FLUXL_16_8.1, J1.123
unnamed: J1.55, J1.56
V_GND: J1.121, J1.122, P1.1
